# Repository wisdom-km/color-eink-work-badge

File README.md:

# P36 当前入口（2026-09-30）

当前新设计为3.6寸六色400×600、手机+USB更新、一体66×109×11.1mm工牌。先读[中文开始说明](docs/portrait/START_HERE.md)。源码评审候选仍有PH/SW3、FPC/C118–C121装配阻断，NFC功能尚未设计完成，未做实体测试，不可制造放行。

P36路径：hardware/portrait/、firmware/portrait36/、docs/portrait/。最终已布线KiCad10原生PCB是铜线权威源；不得运行generate.py/gen_pcb.py/旧import_route.py覆盖铜线，不用pcbnew9保存。新电气修订必须备份并重新完整验证；当前报告仅绑定当前SHA。用户已授权此次重新选型、设计和当前文档同步。

## 以下为H2历史基线范围

以下旧4.2寸/ST25/6.3mm/F2未实现及旧流程仅适用历史H2，不覆盖P36新需求/入口/证据。保留原文供追溯；不要按旧生成命令操作P36。通用中文回复、禁止未经要求PR及许可证要求仍有效。

# chroma-badge（BADGE-42C）：4.2 寸四色墨水屏 NFC 工牌

> **当前：** [状态](docs/06-current-status.md) · [交接](docs/03-handoff.md) · [流程](docs/09-process.md)（许可证 / CI / 贴胶 / 生产包）。2026-09-14 复审是**旧 564 段板**档案，不要当现板。

仓库：https://github.com/wisdom-km/chroma-badge

一块 **6.3 mm 厚**的电子工牌：4.2" 黑白红黄四色墨水屏 + ESP32-C3（Wi-Fi/BLE/原生 USB）+ ST25DV64KC NFC + ≤2 mm 超薄锂电 + USB-C。固件目前是 v0.2 上电自检；手机传图（F2）未写。

| 背面 PCB 渲染 | 外壳（FreeCAD） |
|---|---|
|  | 见 `hardware/enclosure/output/badge_assembly.step` |

## 在本地接着做

```bash
git clone https://github.com/wisdom-km/chroma-badge.git
cd chroma-badge
```

用 Cursor **打开这个文件夹**（本地 Agent）。根目录 `AGENTS.md` 和 `.cursor/rules/badge.mdc` 会带上约定。

## 仓库

- `LICENSE.md`：硬件 CERN-OHL-P-2.0，固件/脚本 MIT
- `AGENTS.md`：硬性约定与当前进度
- `docs/01-architecture-decisions.md`：选型
- `docs/02-bom-and-cost.md`：BOM；屏贴胶 3M 467MP
- `docs/03-handoff.md`：复现步骤与**当前板**指纹
- `docs/09-process.md`：CI、生产包、贴胶
- `hardware/pcb/`：由 `scripts/design.py` 生成
- `firmware/README.md`：v0.2 自检；不要覆盖 `output/badge-42c-v0.1*.bin`

## 快速开始

全量 ERC/DRC 需要 KiCad **10.0.6**。不要把 `gen_pcb.py` 当日常命令（会清布线）。日常检查：

```bash
cd hardware/pcb
python3 scripts/check_netlist.py
./scripts/export.sh --check-only
```

自动布线流程见 `docs/03-handoff.md` 第 3 节。

## 状态

**H2（2026-09-15）：** 58 封装，PCB **680 段 / 115 过孔**，J1.7 NC。KiCad 10.0.6 全量 ERC/DRC 0。USB **0.8 mm**。固件 **v0.2 F1**。没有生产 zip。

下一步：打样实机；F2 须选定一条传图路线。

## 第三方内容

- 乐鑫 KiCad 库（ESP32-C3-MINI-1）：CC-BY-SA 4.0
- HRO TYPE-C-31-M-14 封装：jenschr/USB-C-Connectors，公有领域
- 其余符号/封装来自 KiCad 官方库

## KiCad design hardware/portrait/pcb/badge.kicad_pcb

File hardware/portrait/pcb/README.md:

# P36 当前电气工程

KiCad10.0.6打开badge.kicad_pro。3.6E六色50针参考电路，非H2旧24针屏。原生已布线badge.kicad_pcb是最终铜线权威源；81封装、968线段、115过孔、10区，板58×92.64×0.8mm，元件B面。

最终证据在仓库根verification/visible-final：DRC/未连/原理图parity0，ignored为空；ERC0错误9条逐项审阅single_global_label警告。81元件/259连接pin/28NC对源一致，warning-review.json保留线端点证据。五页为主索引、usb_mcu、power、boost、display。

设计源scripts/design.py、readable_schematic.py与pinned库均可编辑；不要为检查调用generate.py/gen_pcb.py/import_route.py，它们可能清布线。不要用系统pcbnew9保存本10版板。任何新电气/布线修订须新备份及全量ERC/DRC/parity，原证据不能沿用。

屏关电后SPI控制脚停LOW，BUSY无上拉。独立逻辑/boost磁珠，C100在V_B。电池PH pin1GND/pin2VBAT，仍必须量来料；USB HRO额定1A、0.75对0.8板厚实配待测。充电100mA无电芯NTC。完整采购MPN候选见docs/portrait/procurement_candidates.csv；candidate_bom.csv只是五列工程导出。

当前NFC功能未设计/未集成。PH/SW3和FPC/C118–121空间阻断仍需修订或实物几何证明，EDA0不能放行制造。参见docs/portrait/START_HERE.md。

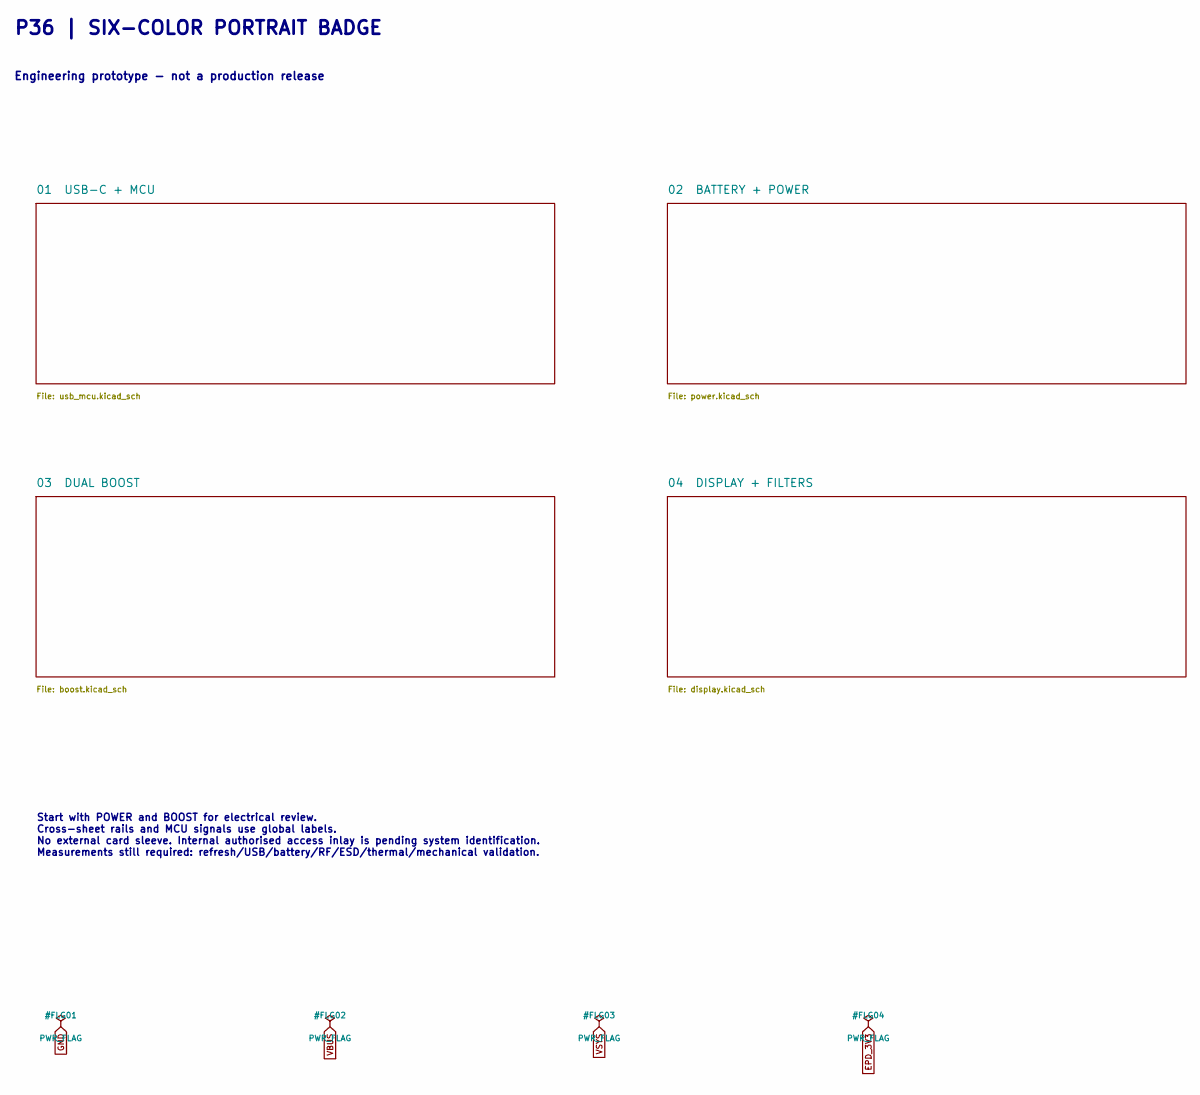
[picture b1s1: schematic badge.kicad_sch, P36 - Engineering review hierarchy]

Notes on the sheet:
P36 | SIX-COLOR PORTRAIT BADGE
Engineering prototype - not a production release
Start with POWER and BOOST for electrical review. Cross-sheet rails and MCU signals use global labels. No external card sleeve. Internal authorised access inlay is pending system identification. Measurements still required: refresh/USB/battery/RF/ESD/thermal/mechanical validation.

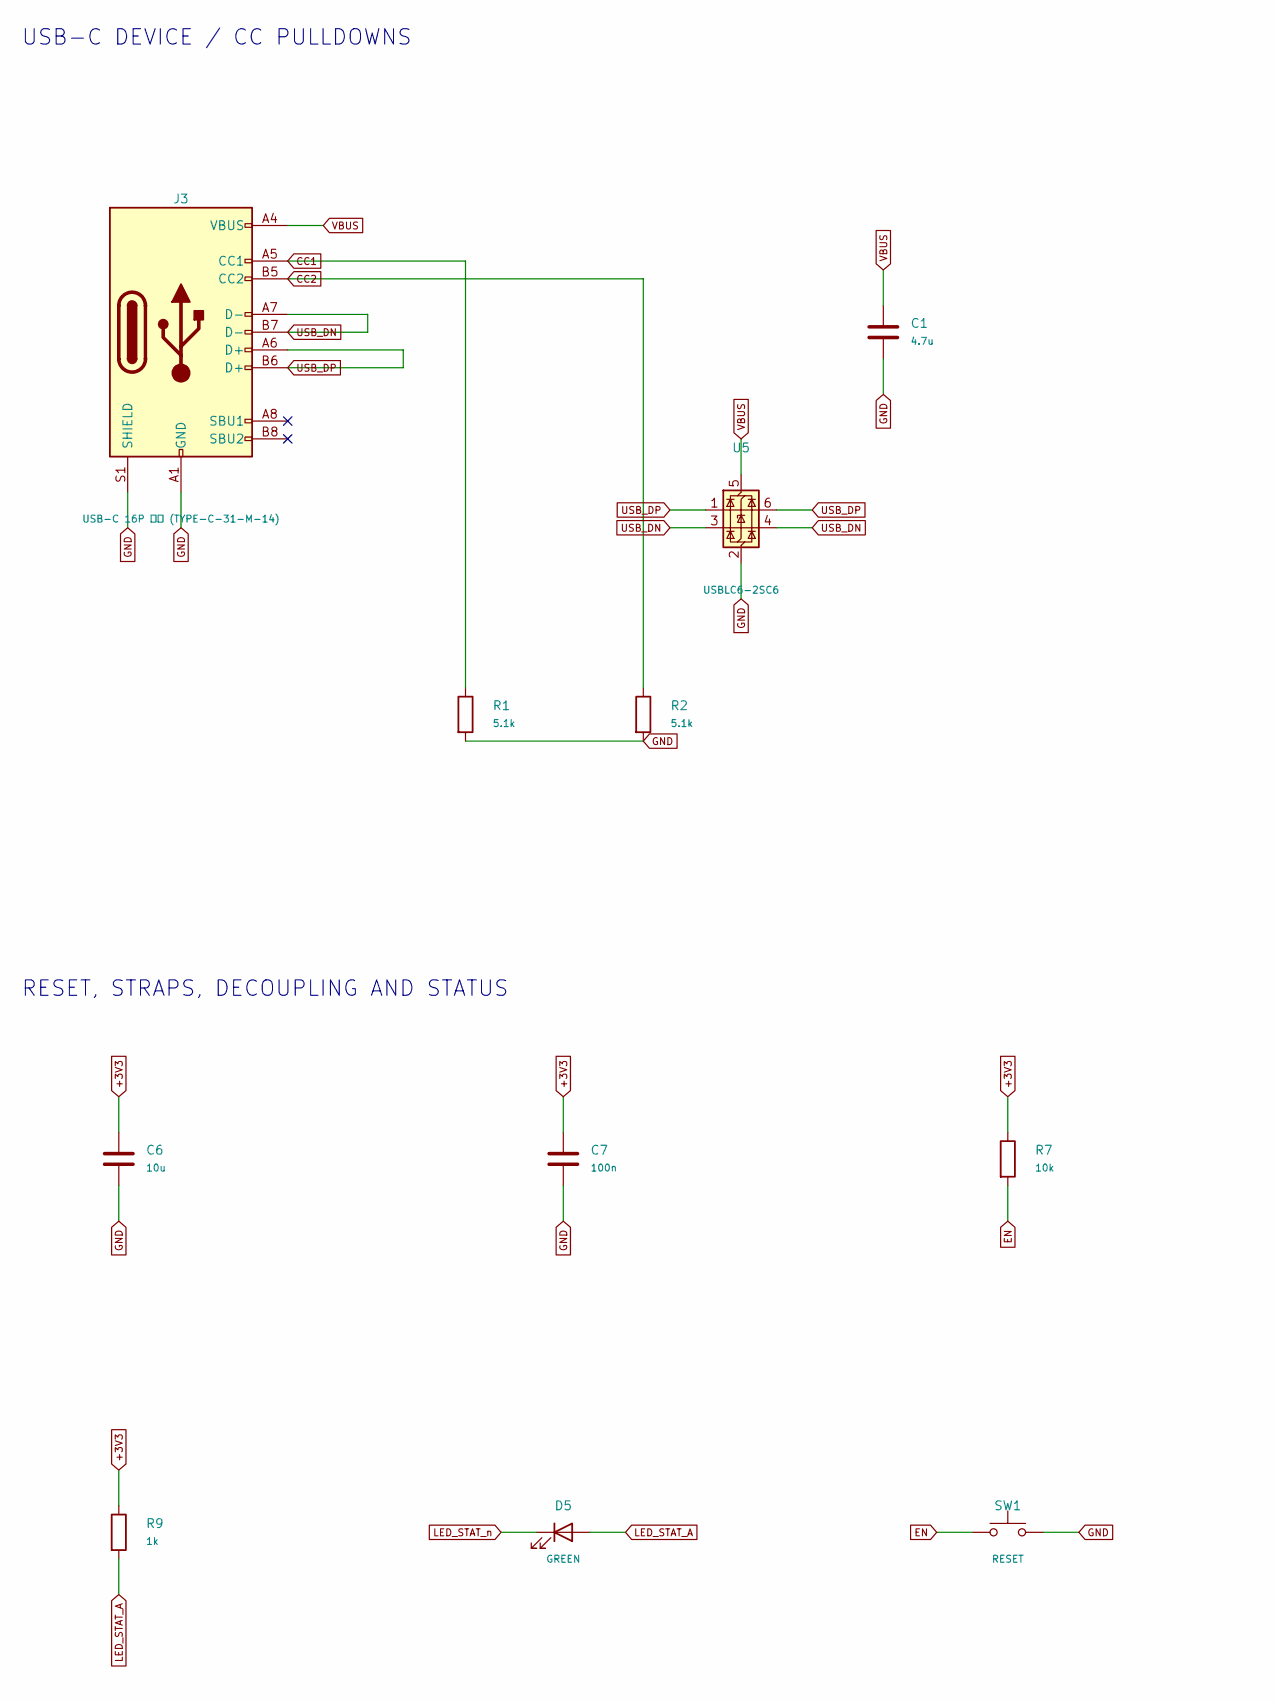
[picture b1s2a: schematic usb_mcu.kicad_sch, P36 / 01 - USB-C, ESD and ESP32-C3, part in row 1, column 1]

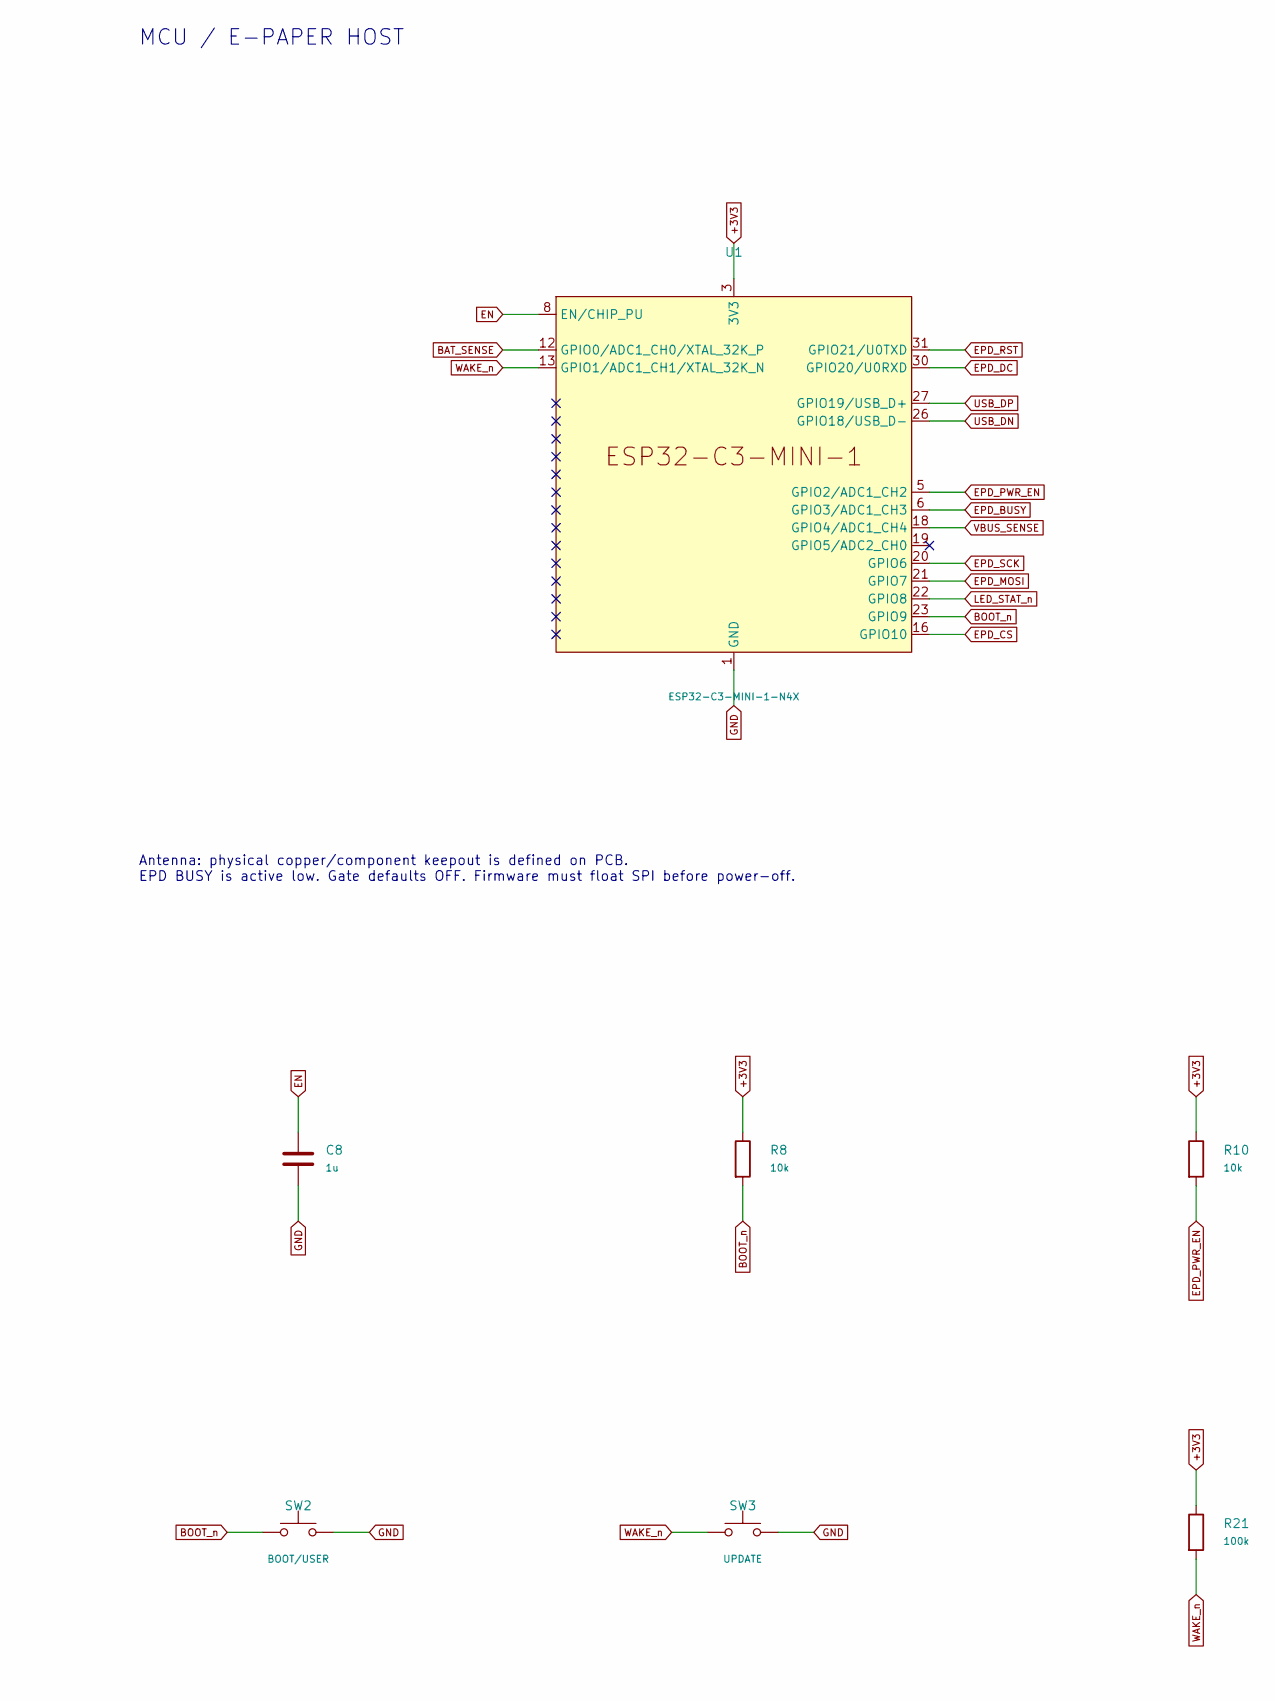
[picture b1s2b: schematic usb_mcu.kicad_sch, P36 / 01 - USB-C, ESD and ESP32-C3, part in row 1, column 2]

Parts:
C1: 4.7u; C_0603_1608Metric
C6: 10u; C_0603_1608Metric
C7: 100n; C_0402_1005Metric
C8: 1u; C_0402_1005Metric
D5: GREEN; LED_0603_1608Metric
J3: USB-C 16P 沉板 (TYPE-C-31-M-14); TYPE-C-31-M-14; LCSC C223907
R1, R2: 5.1k; R_0402_1005Metric
R7, R8, R10: 10k; R_0402_1005Metric
R9: 1k; R_0402_1005Metric
R21: 100k; R_0402_1005Metric
SW1: RESET; SW_SPST_PTS810; LCSC C221929
SW2: BOOT/USER; SW_SPST_PTS810; LCSC C221929
SW3: UPDATE; SW_SPST_PTS810
U1: ESP32-C3-MINI-1-N4X; ESP32-C3-MINI-1
U5: USBLC6-2SC6; SOT-23-6

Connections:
+3V3: C6.1, C7.1, R7.1, R8.1, R9.1, R10.1, R21.1, U1.3 (3V3); also elsewhere on the board
BAT_SENSE: U1.12 (GPIO0/ADC1_CH0/XTAL_32K_P); also elsewhere on the board
BOOT_n: R8.2, SW2.1, U1.23 (GPIO9)
CC1: J3.A5 (CC1), R1.1
CC2: J3.B5 (CC2), R2.1
EN: C8.1, R7.2, SW1.1, U1.8 (EN/CHIP_PU)
EPD_BUSY: U1.6 (GPIO3/ADC1_CH3); also elsewhere on the board
EPD_CS: U1.16 (GPIO10); also elsewhere on the board
EPD_DC: U1.30 (GPIO20/U0RXD); also elsewhere on the board
EPD_MOSI: U1.21 (GPIO7); also elsewhere on the board
EPD_PWR_EN: R10.2, U1.5 (GPIO2/ADC1_CH2); also elsewhere on the board
EPD_RST: U1.31 (GPIO21/U0TXD); also elsewhere on the board
EPD_SCK: U1.20 (GPIO6); also elsewhere on the board
GND: C1.2, C6.2, C7.2, C8.2, J3.A1 (GND), J3.A12 (GND), J3.B1 (GND), J3.B12 (GND), J3.S1 (SHIELD), R1.2, R2.2, SW1.2, SW2.2, SW3.2, U1.1 (GND), U1.2 (GND), U1.11 (GND), U1.14 (GND), U1.36 (GND), U1.37 (GND), U1.38 (GND), U1.39 (GND), U1.40 (GND), U1.41 (GND), U1.42 (GND), U1.43 (GND), U1.44 (GND), U1.45 (GND), U1.46 (GND), U1.47 (GND), U1.48 (GND), U1.49 (GND), U1.50 (GND), U1.51 (GND), U1.52 (GND), U1.53 (GND), U5.2 (GND); also elsewhere on the board
LED_STAT_A: D5.2 (A), R9.2
LED_STAT_n: D5.1 (K), U1.22 (GPIO8)
USB_DN: J3.A7 (D-), J3.B7 (D-), U1.26 (GPIO18/USB_D-), U5.3 (I/O2), U5.4 (I/O2)
USB_DP: J3.A6 (D+), J3.B6 (D+), U1.27 (GPIO19/USB_D+), U5.1 (I/O1), U5.6 (I/O1)
VBUS: C1.1, J3.A4 (VBUS), J3.A9 (VBUS), J3.B4 (VBUS), J3.B9 (VBUS), U5.5 (VBUS); also elsewhere on the board
VBUS_SENSE: U1.18 (GPIO4/ADC1_CH4); also elsewhere on the board
WAKE_n: R21.2, SW3.1, U1.13 (GPIO1/ADC1_CH1/XTAL_32K_N)

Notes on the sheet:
USB-C DEVICE / CC PULLDOWNS
MCU / E-PAPER HOST
Antenna: physical copper/component keepout is defined on PCB. EPD BUSY is active low. Gate defaults OFF. Firmware must float SPI before power-off.
RESET, STRAPS, DECOUPLING AND STATUS

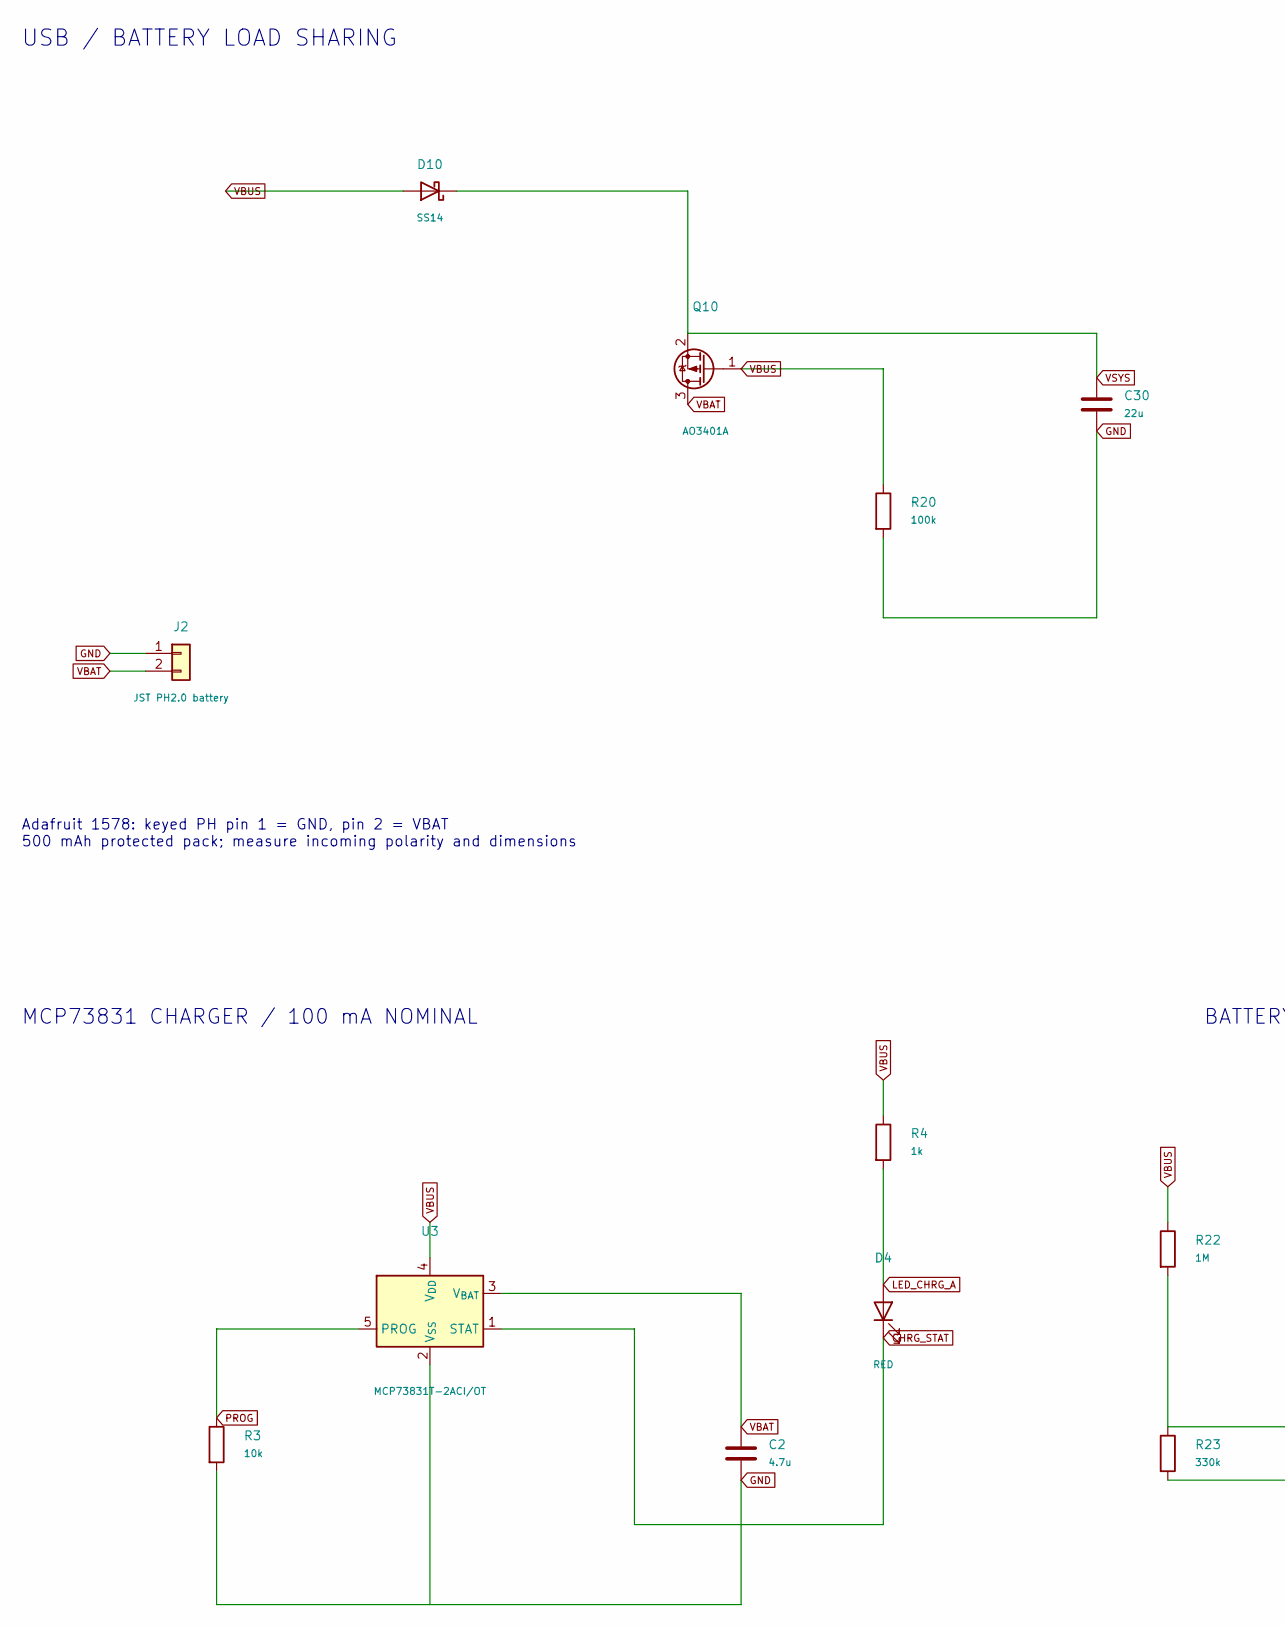
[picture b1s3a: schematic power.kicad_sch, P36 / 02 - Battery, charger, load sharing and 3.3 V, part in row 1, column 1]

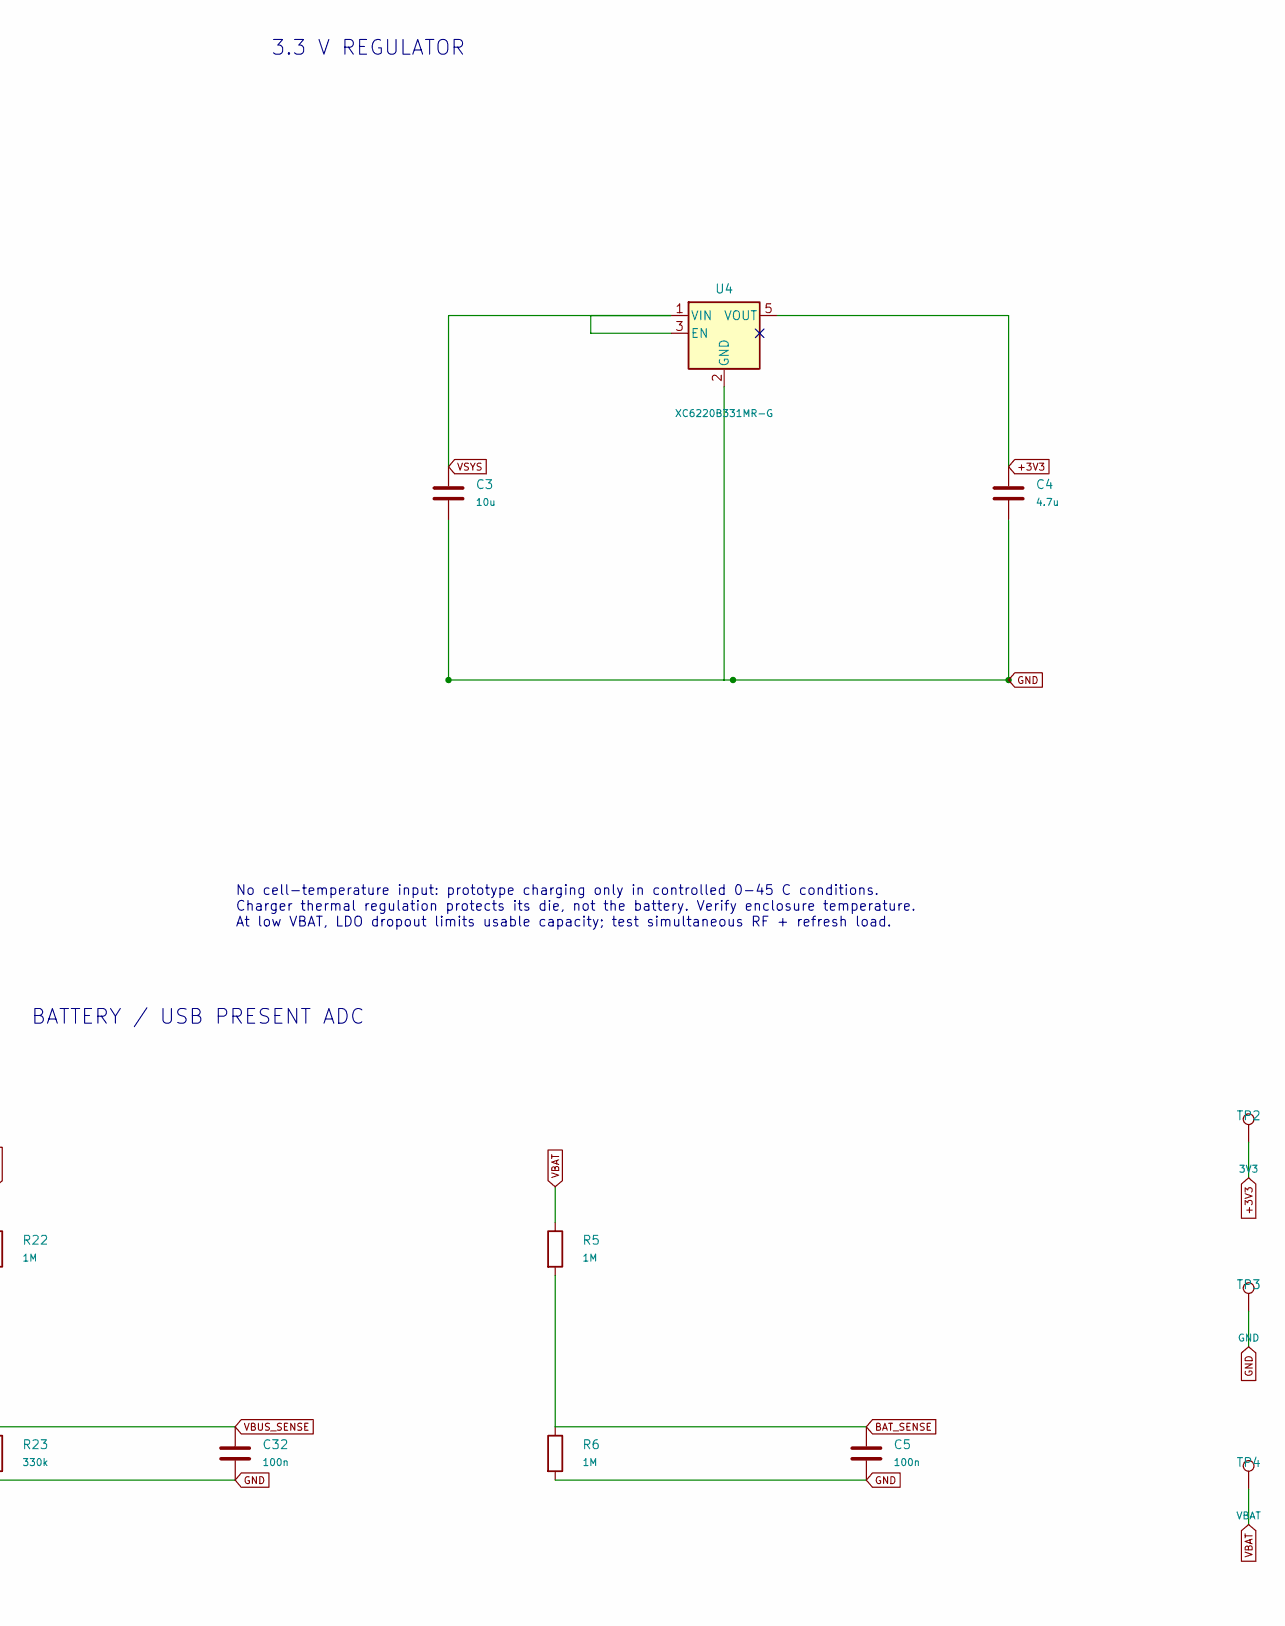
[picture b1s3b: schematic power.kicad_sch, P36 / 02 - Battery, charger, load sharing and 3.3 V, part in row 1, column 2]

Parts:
C2, C4: 4.7u; C_0603_1608Metric
C3: 10u; C_0603_1608Metric
C5, C32: 100n; C_0402_1005Metric
C30: 22u; C_0805_2012Metric
D4: RED; LED_0603_1608Metric
D10: SS14; D_SMA
J2: JST PH2.0 battery; JST_PH_S2B-PH-SM4-TB_1x02-1MP_P2.00mm_Horizontal
Q10: AO3401A; SOT-23
R3: 10k; R_0402_1005Metric
R4: 1k; R_0402_1005Metric
R5, R6, R22: 1M; R_0402_1005Metric
R20: 100k; R_0402_1005Metric
R23: 330k; R_0402_1005Metric
TP2: 3V3; TestPoint_Pad_D1.0mm
TP3: GND; TestPoint_Pad_D1.0mm
TP4: VBAT; TestPoint_Pad_D1.0mm
U3: MCP73831T-2ACI/OT; SOT-23-5
U4: XC6220B331MR-G; SOT-23-5; LCSC C86534

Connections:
+3V3: C4.1, TP2.1, U4.5 (VOUT); also elsewhere on the board
BAT_SENSE: C5.1, R5.2, R6.1; also elsewhere on the board
CHRG_STAT: D4.1 (K), U3.1 (STAT)
GND: C2.2, C3.2, C4.2, C5.2, C30.2, C32.2, J2.1, R3.2, R6.2, R20.2, R23.2, TP3.1, U3.2 (V_{SS}), U4.2 (GND); also elsewhere on the board
LED_CHRG_A: D4.2 (A), R4.2
PROG: R3.1, U3.5 (PROG)
VBAT: C2.1, J2.2, Q10.3 (D), R5.1, TP4.1, U3.3 (V_{BAT})
VBUS: D10.2 (A), Q10.1 (G), R4.1, R20.1, R22.1, U3.4 (V_{DD}); also elsewhere on the board
VBUS_SENSE: C32.1, R22.2, R23.1; also elsewhere on the board
VSYS: C3.1, C30.1, D10.1 (K), Q10.2 (S), U4.1 (VIN), U4.3 (EN)

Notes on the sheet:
USB / BATTERY LOAD SHARING
Adafruit 1578: keyed PH pin 1 = GND, pin 2 = VBAT 500 mAh protected pack; measure incoming polarity and dimensions
MCP73831 CHARGER / 100 mA NOMINAL
3.3 V REGULATOR
BATTERY / USB PRESENT ADC
No cell-temperature input: prototype charging only in controlled 0-45 C conditions. Charger thermal regulation protects its die, not the battery. Verify enclosure temperature. At low VBAT, LDO dropout limits usable capacity; test simultaneous RF + refresh load.

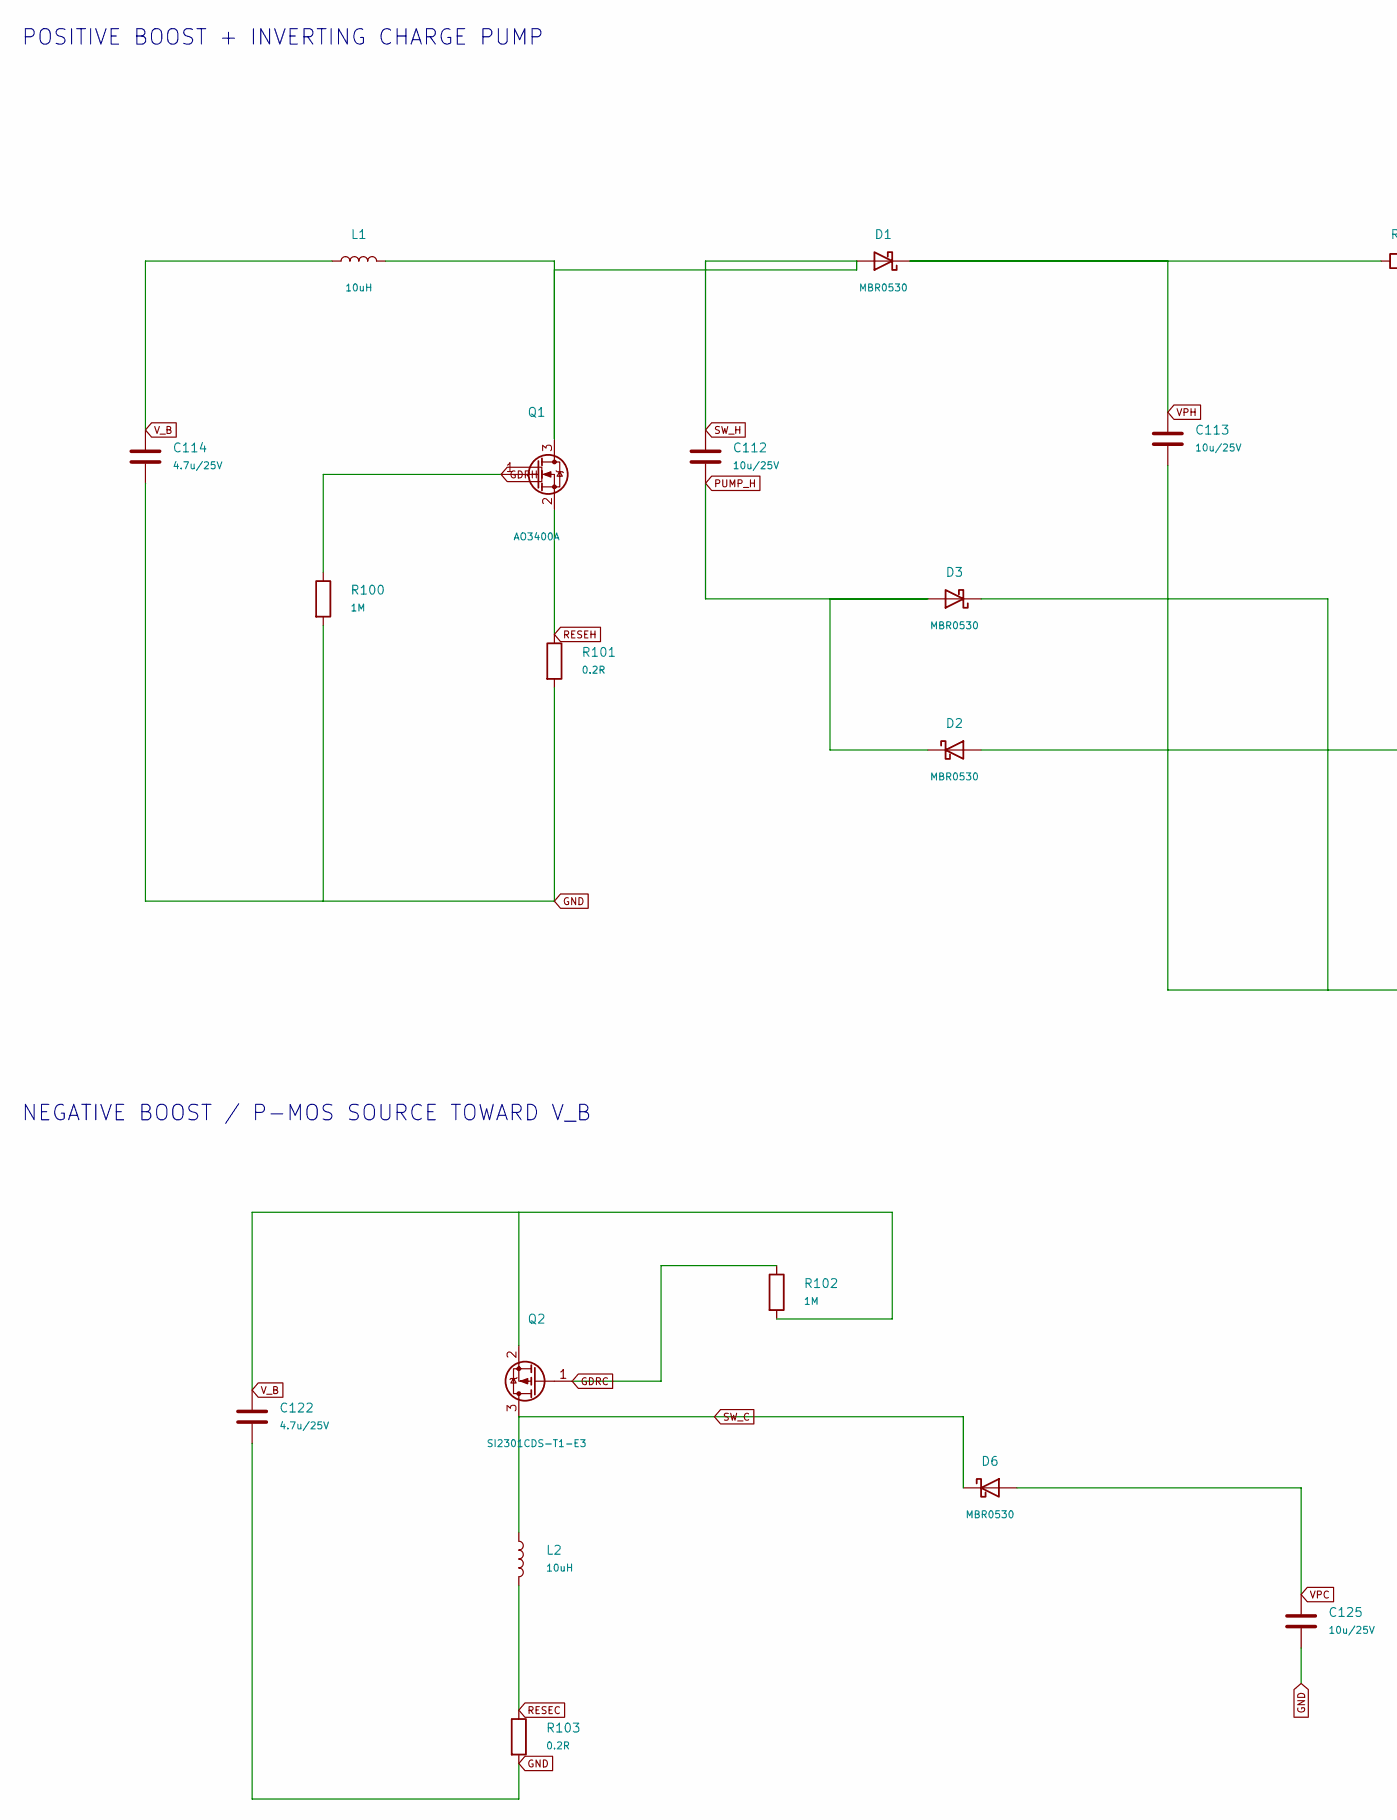
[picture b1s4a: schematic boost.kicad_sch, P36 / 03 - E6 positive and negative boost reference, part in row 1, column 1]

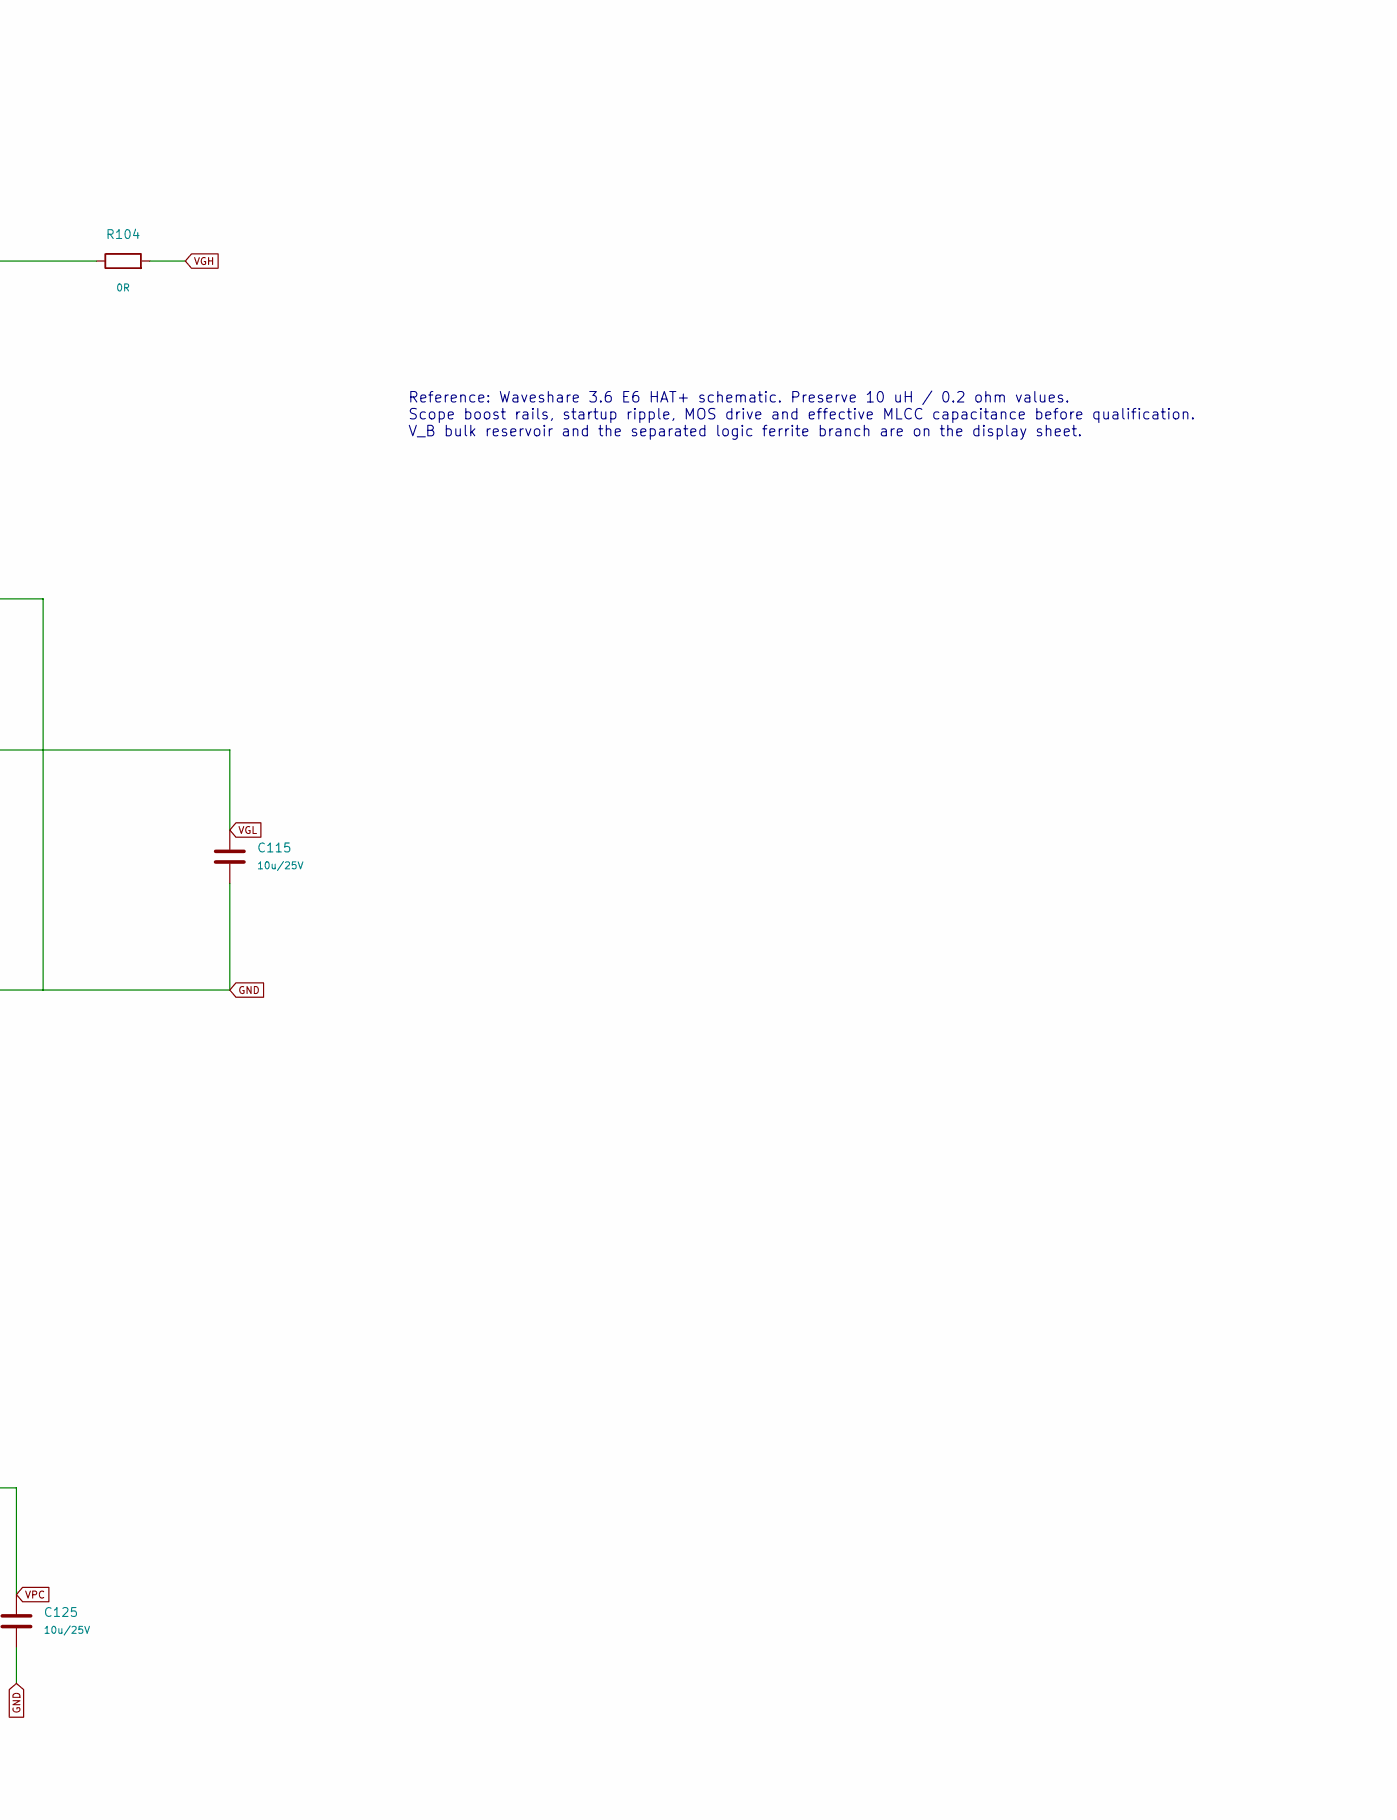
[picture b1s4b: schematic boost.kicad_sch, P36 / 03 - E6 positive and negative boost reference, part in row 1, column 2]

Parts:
C112, C113, C115, C125: 10u/25V; C_0805_2012Metric
C114, C122: 4.7u/25V; C_0805_2012Metric
D1, D2, D3, D6: MBR0530; D_SOD-123
L1, L2: 10uH; L_Changjiang_FNR4018S
Q1: AO3400A; SOT-23
Q2: SI2301CDS-T1-E3; SOT-23
R100, R102: 1M; R_0603_1608Metric
R101, R103: 0.2R; R_0805_2012Metric
R104: 0R; R_0603_1608Metric

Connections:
GDRC: Q2.1 (G), R102.1; also elsewhere on the board
GDRH: Q1.1 (G), R100.1; also elsewhere on the board
GND: C113.2, C114.2, C115.2, C122.2, C125.2, D3.1 (K), R100.2, R101.2, R103.2; also elsewhere on the board
PUMP_H: C112.2, D2.1 (K), D3.2 (A)
RESEC: L2.2, R103.1; also elsewhere on the board
RESEH: Q1.2 (S), R101.1; also elsewhere on the board
SW_C: D6.1 (K), L2.1, Q2.3 (D)
SW_H: C112.1, D1.2 (A), L1.2, Q1.3 (D)
VGH: R104.2; also elsewhere on the board
VGL: C115.1, D2.2 (A); also elsewhere on the board
VPC: C125.1, D6.2 (A); also elsewhere on the board
VPH: C113.1, D1.1 (K), R104.1; also elsewhere on the board
V_B: C114.1, C122.1, L1.1, Q2.2 (S), R102.2; also elsewhere on the board

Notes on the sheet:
POSITIVE BOOST + INVERTING CHARGE PUMP
NEGATIVE BOOST / P-MOS SOURCE TOWARD V_B
Reference: Waveshare 3.6 E6 HAT+ schematic. Preserve 10 uH / 0.2 ohm values. Scope boost rails, startup ripple, MOS drive and effective MLCC capacitance before qualification. V_B bulk reservoir and the separated logic ferrite branch are on the display sheet.
